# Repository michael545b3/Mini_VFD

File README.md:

# Mini VFD based on STM32

This project is a compact Variable Frequency Drive (VFD) built around an  
STM32 microcontroller and an ST IPM (Intelligent Power Module).  
It is designed to control small AC motors efficiently and safely in a compact form factor.

---

## Hardware Overview

### Core Components
- **STM32F407** microcontroller
- **STGIPN3H60** IPM (Intelligent Power Module)
- **High-voltage measurement**
- **Analog inputs** for control signals
- **Opto-isolated digital inputs**
- **Relay output**
- **EEPROM** for parameter storage

### Power Supply
- **Flyback converter** for isolated supply
- **E-Fuse** for protection
- **Buck converter** with **LDOs** for logic power

### User Interface
- **LCD display**
- **Push buttons** and **rotary encoder** for input

---

## Software Status

The firmware is currently under development. As a hardware-focused developer,  
progress is steady but slow — writing robust embedded software takes time.

So far, the implemented functions run reliably, and more features are being added continuously.  
A demonstration video will be available soon.

---

## Roadmap / To-Do

- [ ] Motor control tuning
- [ ] UI menu system improvements
- [ ] Fault monitoring and protection
- [ ] IO implementation

---

## Contributions

Contributions, feedback, or suggestions are very welcome!

---

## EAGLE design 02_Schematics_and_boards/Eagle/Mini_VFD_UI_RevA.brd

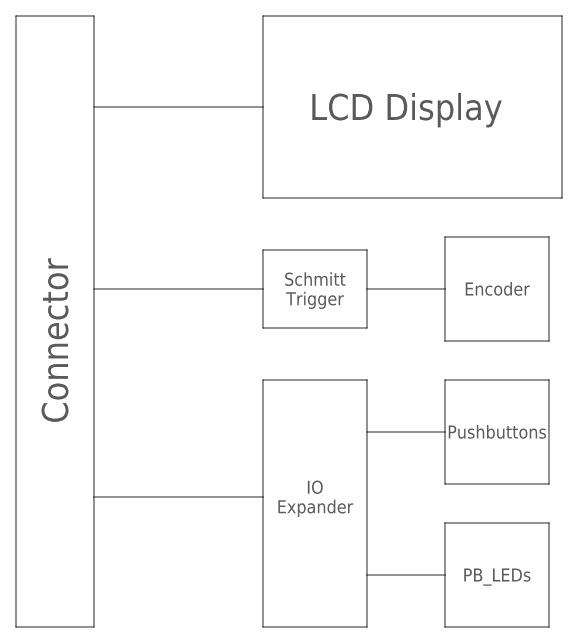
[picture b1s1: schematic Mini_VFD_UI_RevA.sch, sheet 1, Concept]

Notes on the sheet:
LCD Display
Connector
Encoder
IO Expander
Pushbuttons
PB_LEDs
Schmitt Trigger

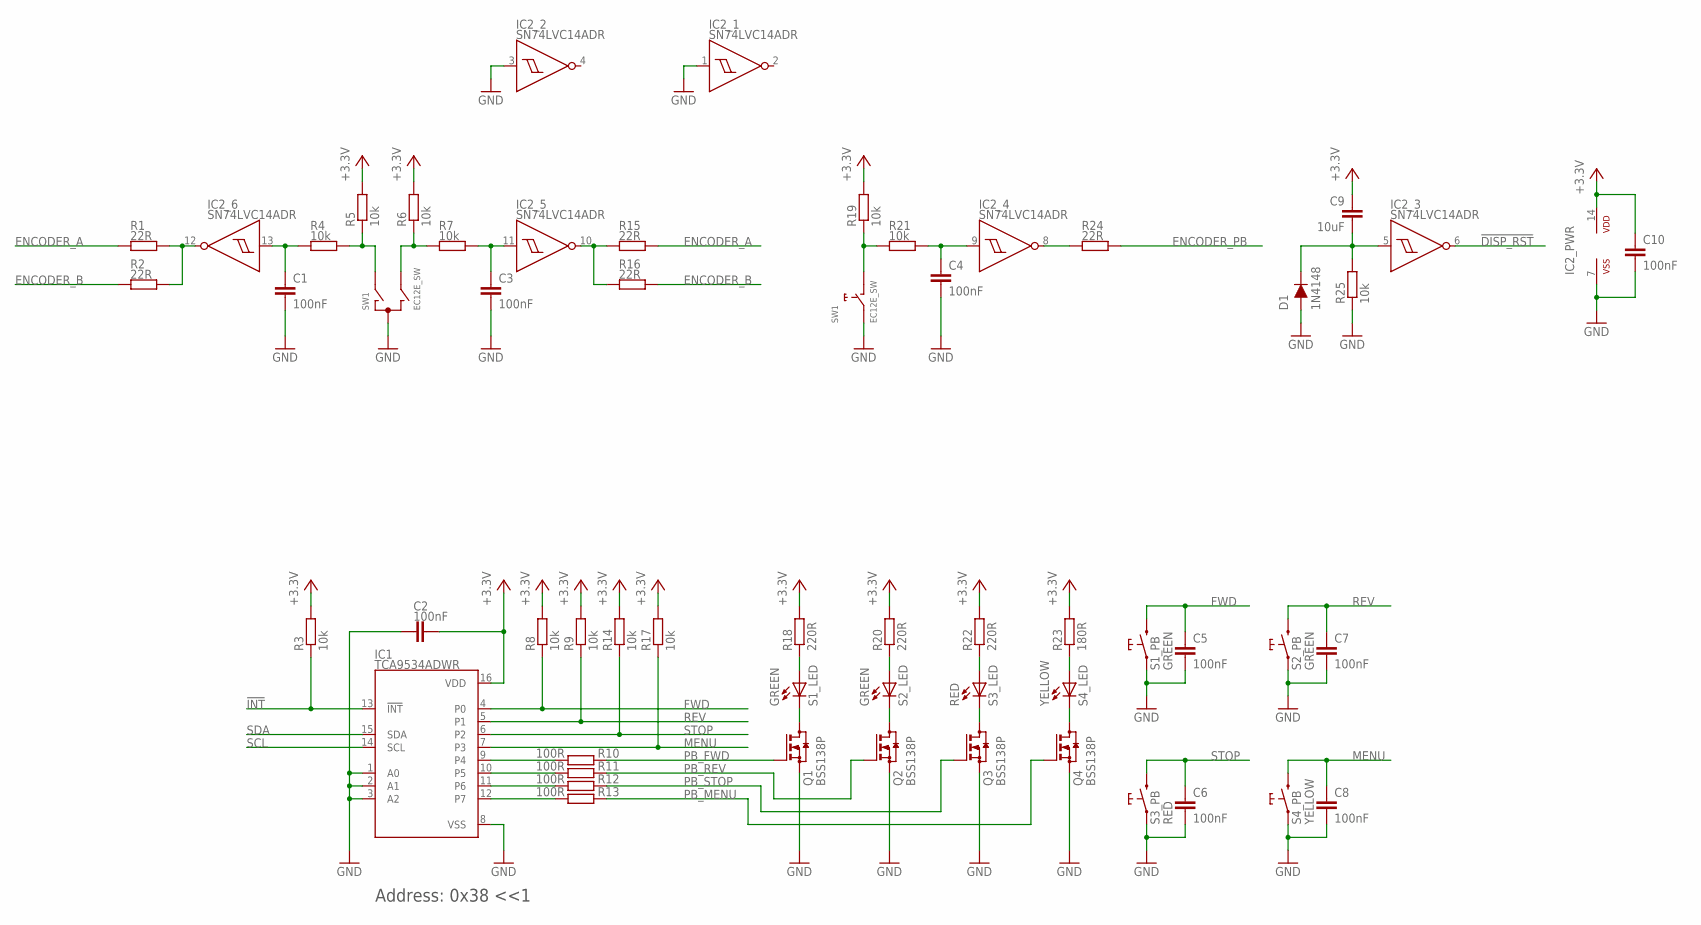
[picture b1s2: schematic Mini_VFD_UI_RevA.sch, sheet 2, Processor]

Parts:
C1, C2, C3, C4, C5, C6, C7, C8, C10: 100nF; C0603
C9: 10uF; C1206
D1: 1N4148; SOD123
IC1: TCA9534ADWR; SOIC16R
IC2: SN74LVC14ADR; SO14
Q1, Q2, Q3, Q4: BSS138P; SOT23
R1, R2, R15, R16, R24: 22R; R0603
R3, R4, R5, R6, R7, R8, R9, R14, R17, R19, R21, R25: 10k; R0603
R10, R11, R12, R13: 100R; R0603
R18, R20, R22: 220R; R0603
R23: 180R; R0603
S1, S2: GREEN; PB_ALIEXPRESS
S3: RED; PB_ALIEXPRESS
S4: YELLOW; PB_ALIEXPRESS
SW1: EC12E_SW; ALPS_EC12E_SW

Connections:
!DISP_RST: IC2.6 (O); also elsewhere on the board
!INT: IC1.13 (!INT), R3.1; also elsewhere on the board
+3.3V: C2.2, C9.1, C10.1, IC1.16 (VDD), IC2.14 (VDD), R3.2, R5.2, R6.2, R8.2, R9.2, R14.2, R17.2, R18.2, R19.2, R20.2, R22.2, R23.2; also elsewhere on the board
ENCODER_A: R1.1, R15.2; also elsewhere on the board
ENCODER_B: R2.1, R16.2; also elsewhere on the board
ENCODER_PB: R24.2; also elsewhere on the board
FWD: C5.1, IC1.4 (P0), R8.1, S1.2A (2), S1.2B (2)
GND: C1.2, C2.1, C3.2, C4.2, C5.2, C6.2, C7.2, C8.2, C10.2, D1.2 (A), IC1.1 (A0), IC1.2 (A1), IC1.3 (A2), IC1.8 (VSS), IC2.1 (I), IC2.3 (I), IC2.7 (VSS), Q1.2 (S), Q2.2 (S), Q3.2 (S), Q4.2 (S), R25.1, S1.1A (1), S1.1B (1), S2.1A (1), S2.1B (1), S3.1A (1), S3.1B (1), S4.1A (1), S4.1B (1), SW1.C, SW1.E (2); also elsewhere on the board
MENU: C8.1, IC1.7 (P3), R17.1, S4.2A (2), S4.2B (2)
unnamed: R4.2, R5.1, SW1.A
unnamed: R6.1, R7.1, SW1.B
unnamed: C1.1, IC2.13 (I), R4.1
unnamed: C3.1, IC2.11 (I), R7.2
unnamed: R19.1, R21.1, SW1.D (1)
unnamed: C4.1, IC2.9 (I), R21.2
unnamed: IC2.10 (O), R15.1, R16.1
unnamed: IC2.12 (O), R1.2, R2.2
unnamed: C9.2, D1.1 (C), IC2.5 (I), R25.2
unnamed: IC1.12 (P7), R13.1
unnamed: IC1.11 (P6), R12.1
unnamed: IC1.10 (P5), R11.1
unnamed: IC1.9 (P4), R10.1
unnamed: Q1.3 (D), S1.- (C)
unnamed: Q2.3 (D), S2.- (C)
unnamed: Q3.3 (D), S3.- (C)
unnamed: Q4.3 (D), S4.- (C)
unnamed: R18.1, S1.+ (A)
unnamed: R20.1, S2.+ (A)
unnamed: R22.1, S3.+ (A)
unnamed: R23.1, S4.+ (A)
unnamed: IC2.8 (O), R24.1
PB_FWD: Q1.1 (G), R10.2
PB_MENU: Q4.1 (G), R13.2
PB_REV: Q2.1 (G), R11.2
PB_STOP: Q3.1 (G), R12.2
REV: C7.1, IC1.5 (P1), R9.1, S2.2A (2), S2.2B (2)
SCL: IC1.14 (SCL); also elsewhere on the board
SDA: IC1.15 (SDA); also elsewhere on the board
STOP: C6.1, IC1.6 (P2), R14.1, S3.2A (2), S3.2B (2)

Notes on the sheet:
Address: 0x38 <<1

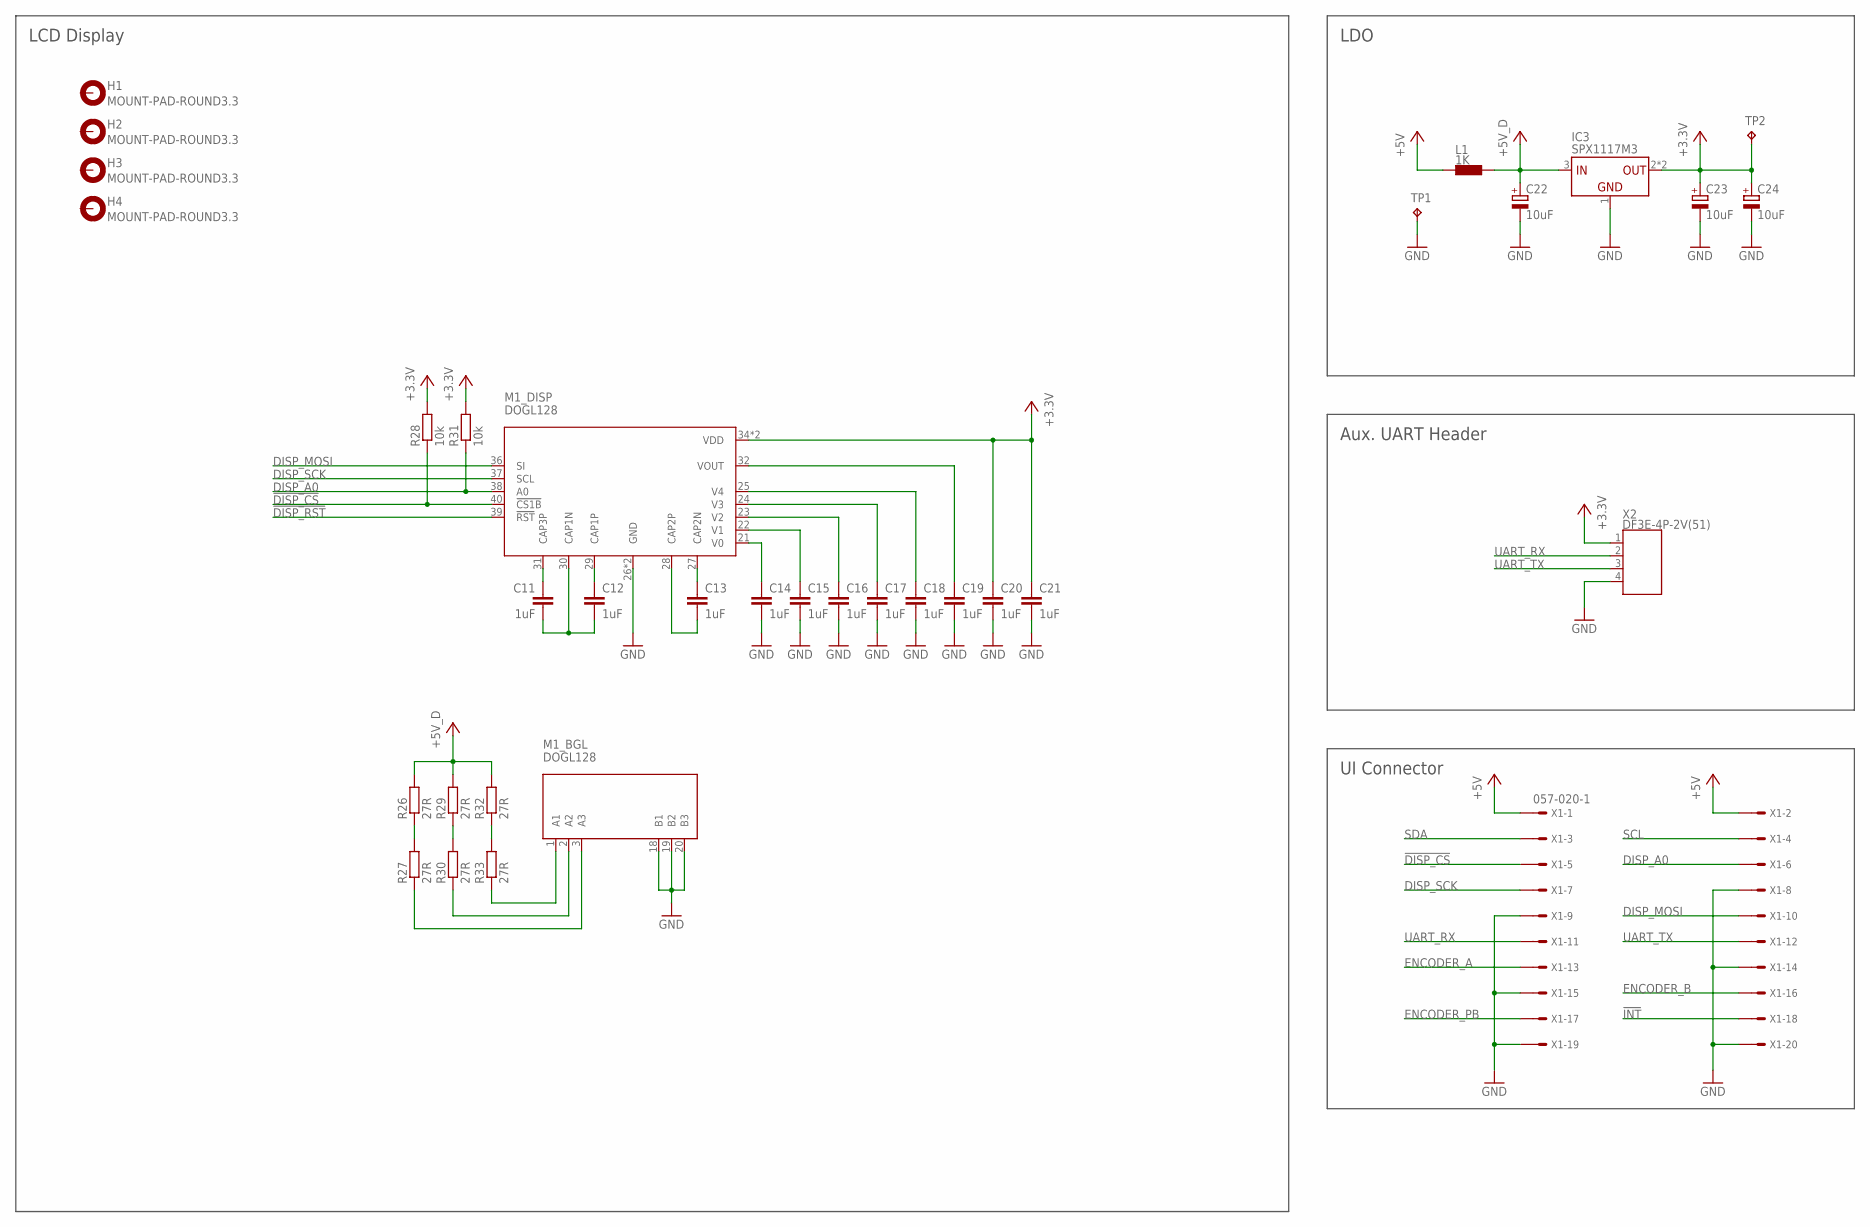
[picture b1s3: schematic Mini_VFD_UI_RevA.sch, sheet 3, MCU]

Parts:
C11, C12, C13, C14, C15, C16, C17, C18, C19, C20, C21: 1uF; C0603
C22, C23, C24: 10uF; CT3528
H1, H2, H3, H4: MOUNT-PAD-ROUND3.3; 3,3-PAD
IC3: SPX1117M3; SOT223
L1: 1K; R0603
M1: DOGL128; DOGL128-6
R26, R27, R29, R30, R32, R33: 27R; R1206
R28, R31: 10k; R0603
TP1, TP2: TPTP10R; TP10R
X1: 057-020-1
X2: DF3E-4P-2V(51); DF3E-4P-2V

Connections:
!DISP_CS: M1.40 (!CS1B), R28.1, X1.5
!DISP_RST: M1.39 (!RST); also elsewhere on the board
!INT: X1.18; also elsewhere on the board
+3.3V: C20.1, C21.1, C23.+, C24.+, IC3.2 (VOUT), IC3.4 (VOUT), M1.34 (VDD), M1.35 (VDD), R28.2, R31.2, TP2.TP, X2.1; also elsewhere on the board
+5V: L1.2, X1.1, X1.2
+5V_D: C22.+, IC3.3 (VIN), L1.1, R26.2, R29.2, R32.2
DISP_A0: M1.38 (A0), R31.1, X1.6
DISP_MOSI: M1.36 (SI), X1.10
DISP_SCK: M1.37 (SCL), X1.7
ENCODER_A: X1.13; also elsewhere on the board
ENCODER_B: X1.16; also elsewhere on the board
ENCODER_PB: X1.17; also elsewhere on the board
GND: C14.2, C15.2, C16.2, C17.2, C18.2, C19.2, C20.2, C21.2, C22.-, C23.-, C24.-, IC3.1 (GND), M1.18 (B1), M1.19 (B2), M1.20 (B3), M1.26 (GND), M1.33 (GND), TP1.TP, X1.8, X1.9, X1.14, X1.15, X1.19, X1.20, X2.4; also elsewhere on the board
unnamed: C13.2, M1.28 (CAP2P)
unnamed: C13.1, M1.27 (CAP2N)
unnamed: C12.1, M1.29 (CAP1P)
unnamed: C11.2, C12.2, M1.30 (CAP1N)
unnamed: C11.1, M1.31 (CAP3P)
unnamed: C14.1, M1.21 (V0)
unnamed: C15.1, M1.22 (V1)
unnamed: C16.1, M1.23 (V2)
unnamed: C17.1, M1.24 (V3)
unnamed: C18.1, M1.25 (V4)
unnamed: C19.1, M1.32 (VOUT)
unnamed: R26.1, R27.2
unnamed: M1.3 (A3), R27.1
unnamed: M1.2 (A2), R30.1
unnamed: M1.1 (A1), R33.1
unnamed: R29.1, R30.2
unnamed: R32.1, R33.2
SCL: X1.4; also elsewhere on the board
SDA: X1.3; also elsewhere on the board
UART_RX: X1.11, X2.2
UART_TX: X1.12, X2.3

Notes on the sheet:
LDO
LCD Display
UI Connector
Aux. UART Header

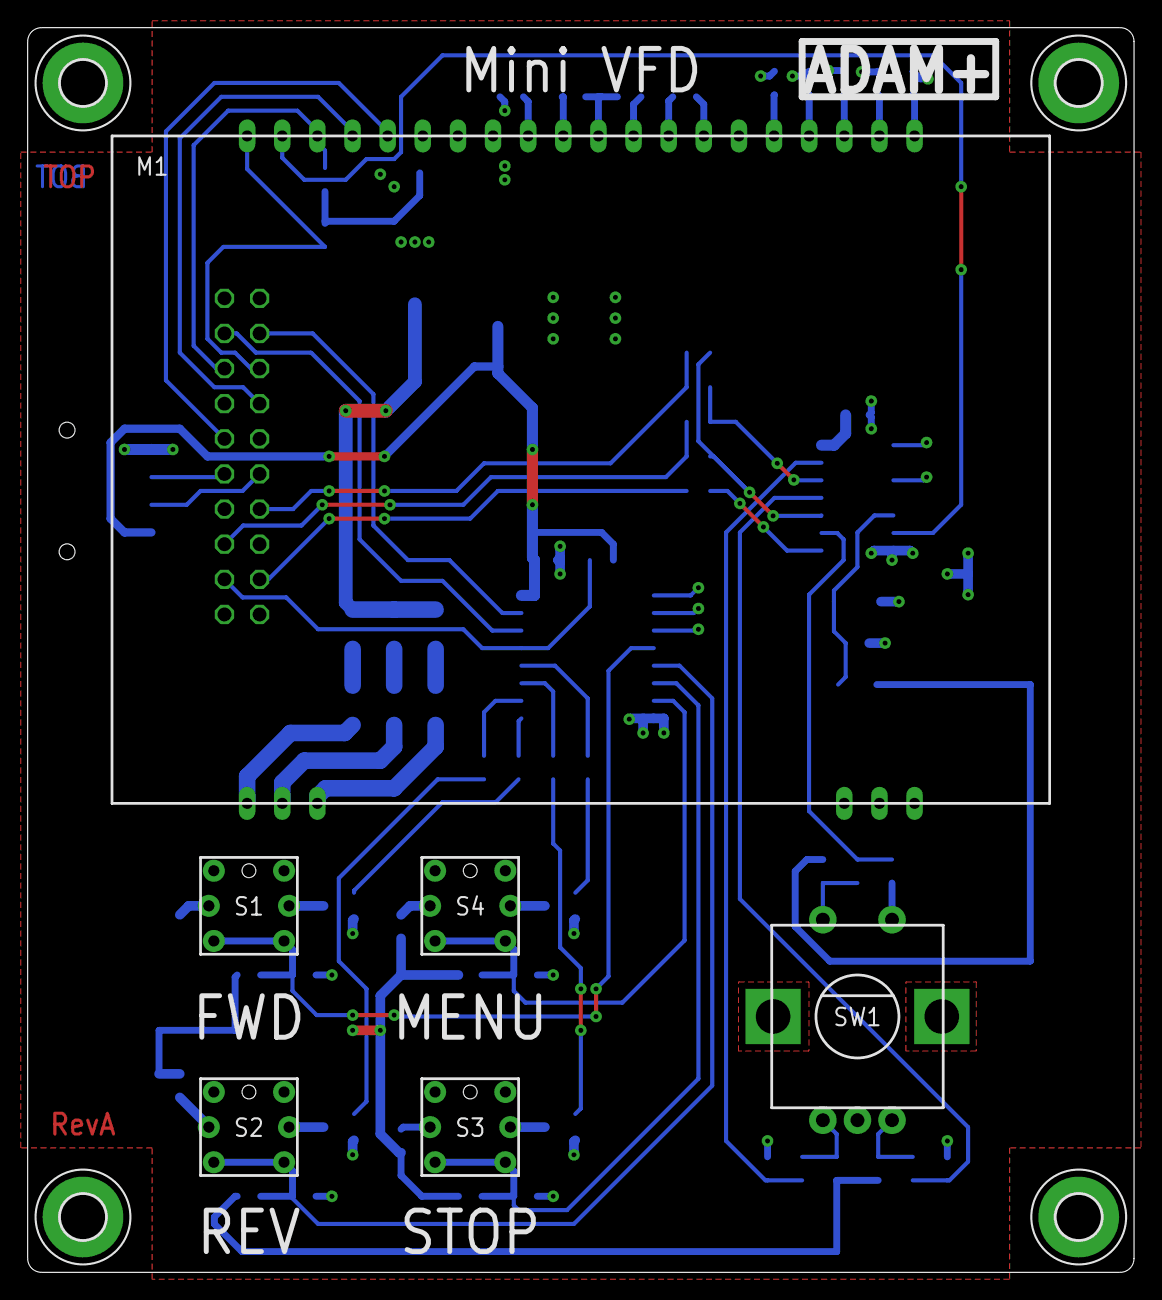
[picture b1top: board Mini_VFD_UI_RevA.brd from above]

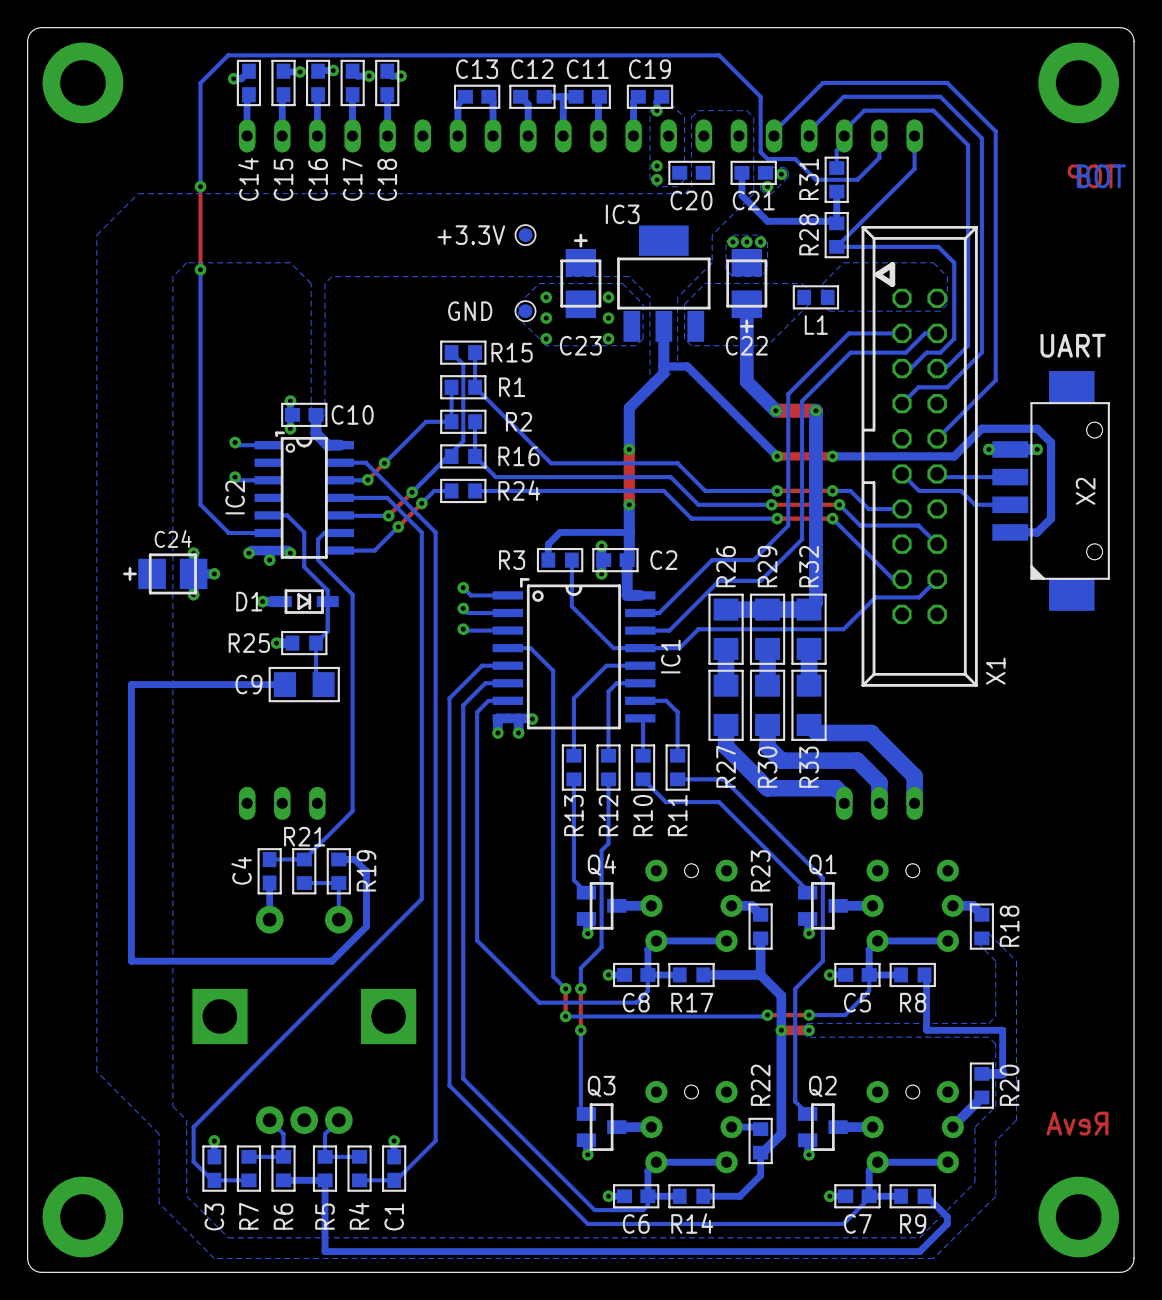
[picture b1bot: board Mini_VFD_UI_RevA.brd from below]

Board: 2 copper layers, 80.0 x 90.0 mm, 80 parts (70 on the bottom side), 64 nets.

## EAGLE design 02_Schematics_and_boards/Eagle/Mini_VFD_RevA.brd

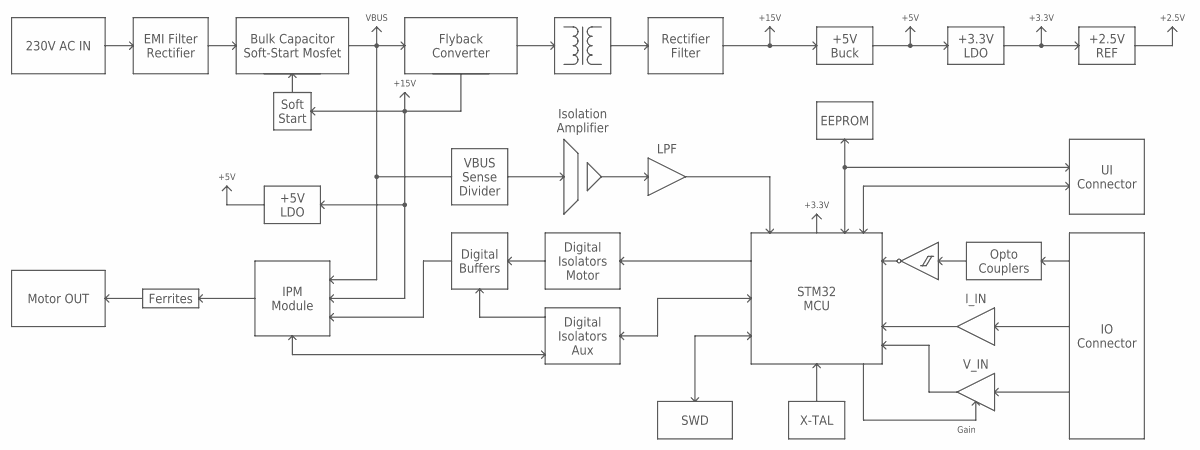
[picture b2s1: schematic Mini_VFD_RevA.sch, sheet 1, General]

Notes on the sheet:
230V AC IN
EMI Filter Rectifier
Bulk Capacitor Soft-Start Mosfet
Soft Start
Flyback Converter
Rectifier Filter
VBUS
+15V
IPM Module
+5V Buck
+3.3V LDO
+5V
+3.3V
Motor OUT
Ferrites
Digital Isolators Motor
STM32 MCU
Opto Couplers
IO Connector
X-TAL
SWD
Digital Buffers
Digital Isolators Aux
+2.5V REF
+2.5V
VBUS Sense Divider
Isolation Amplifier
LPF
I_IN
V_IN
Gain
EEPROM
UI Connector
+5V LDO

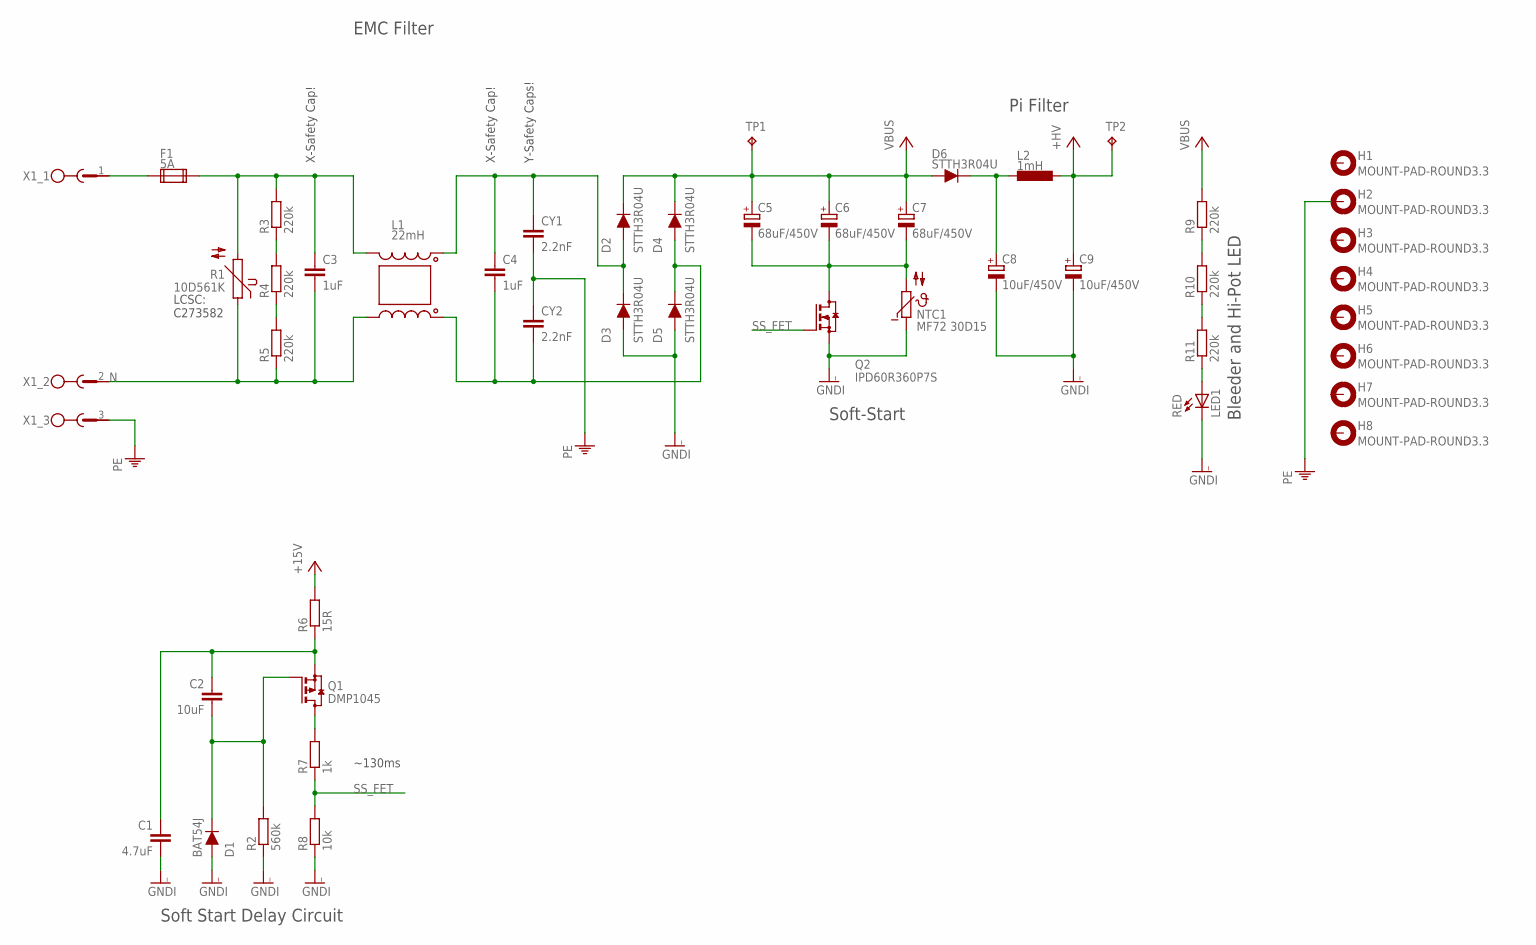
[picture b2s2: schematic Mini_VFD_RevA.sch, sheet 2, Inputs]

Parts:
C1: 4.7uF; C0805
C2: 10uF; C0805
C3, C4: 1uF; C102-082X133
C5, C6, C7: 68uF/450V; E7,5-18
C8, C9: 10uF/450V; E5-10,5
CY1, CY2: 2.2nF; YC7B5
D1: BAT54J; SOD123
D2, D3, D4, D5, D6: STTH3R04U; SMB
F1: 5A; SH25
H1, H2, H3, H4, H5, H6, H7, H8: MOUNT-PAD-ROUND3.3; 3,3-PAD
L1: 22mH; CMC_PDMCAT18107
L2: 1mH; SLH0704
LED1: RED; LED_0805
NTC1: MF72 30D15; MF72
Q1: DMP1045; SOT23
Q2: IPD60R360P7S; TO252
R1: 10D561K; S10K175
R2: 560k; R0603
R3, R4, R5, R9, R10, R11: 220k; R1206
R6: 15R; 0207/10
R7: 1k; R0603
R8: 10k; R0603
TP1, TP2: TPTP10R; TP10R
X1: MSTBV3

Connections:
+15V: R6.2; also elsewhere on the board
+HV: C9.+, L2.1, TP2.TP; also elsewhere on the board
C_NEG: C5.-, C6.-, C7.-, NTC1.2, Q2.3 (D)
GNDI: C1.2, C8.-, C9.-, D1.2 (A), D3.A, D5.A, LED1.C, NTC1.1, Q2.2 (S), R2.1, R8.1; also elsewhere on the board
L: F1.1, X1.1
L_FILT: C4.1, CY1.1, D2.A, D3.C, L1.IN1
L_FUSED: C3.1, F1.2, L1.OUT1, R1.2, R3.2
N: C3.2, L1.OUT2, R1.1, R5.1, X1.2
unnamed: Q1.3 (D), R7.2
unnamed: C2.2, D1.1 (C), Q1.1 (G), R2.2
unnamed: C1.1, C2.1, Q1.2 (S), R6.1
unnamed: R3.1, R4.2
unnamed: R4.1, R5.2
unnamed: R9.1, R10.2
unnamed: R10.1, R11.2
unnamed: LED1.A, R11.1
N_FILT: C4.2, CY2.2, D4.A, D5.C, L1.IN2
PE: CY1.2, CY2.1, H2.B3,3, X1.3; also elsewhere on the board
SS_FET: Q2.1 (G), R7.1, R8.2
VBUS: C5.+, C6.+, C7.+, D2.C, D4.C, D6.A, R9.2, TP1.TP; also elsewhere on the board
VBUS_FILT: C8.+, D6.C, L2.2

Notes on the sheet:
LCSC: C273582
X-Safety Cap!
Y-Safety Caps!
Soft-Start
Pi Filter
Bleeder and Hi-Pot LED
Soft Start Delay Circuit
~130ms
EMC Filter

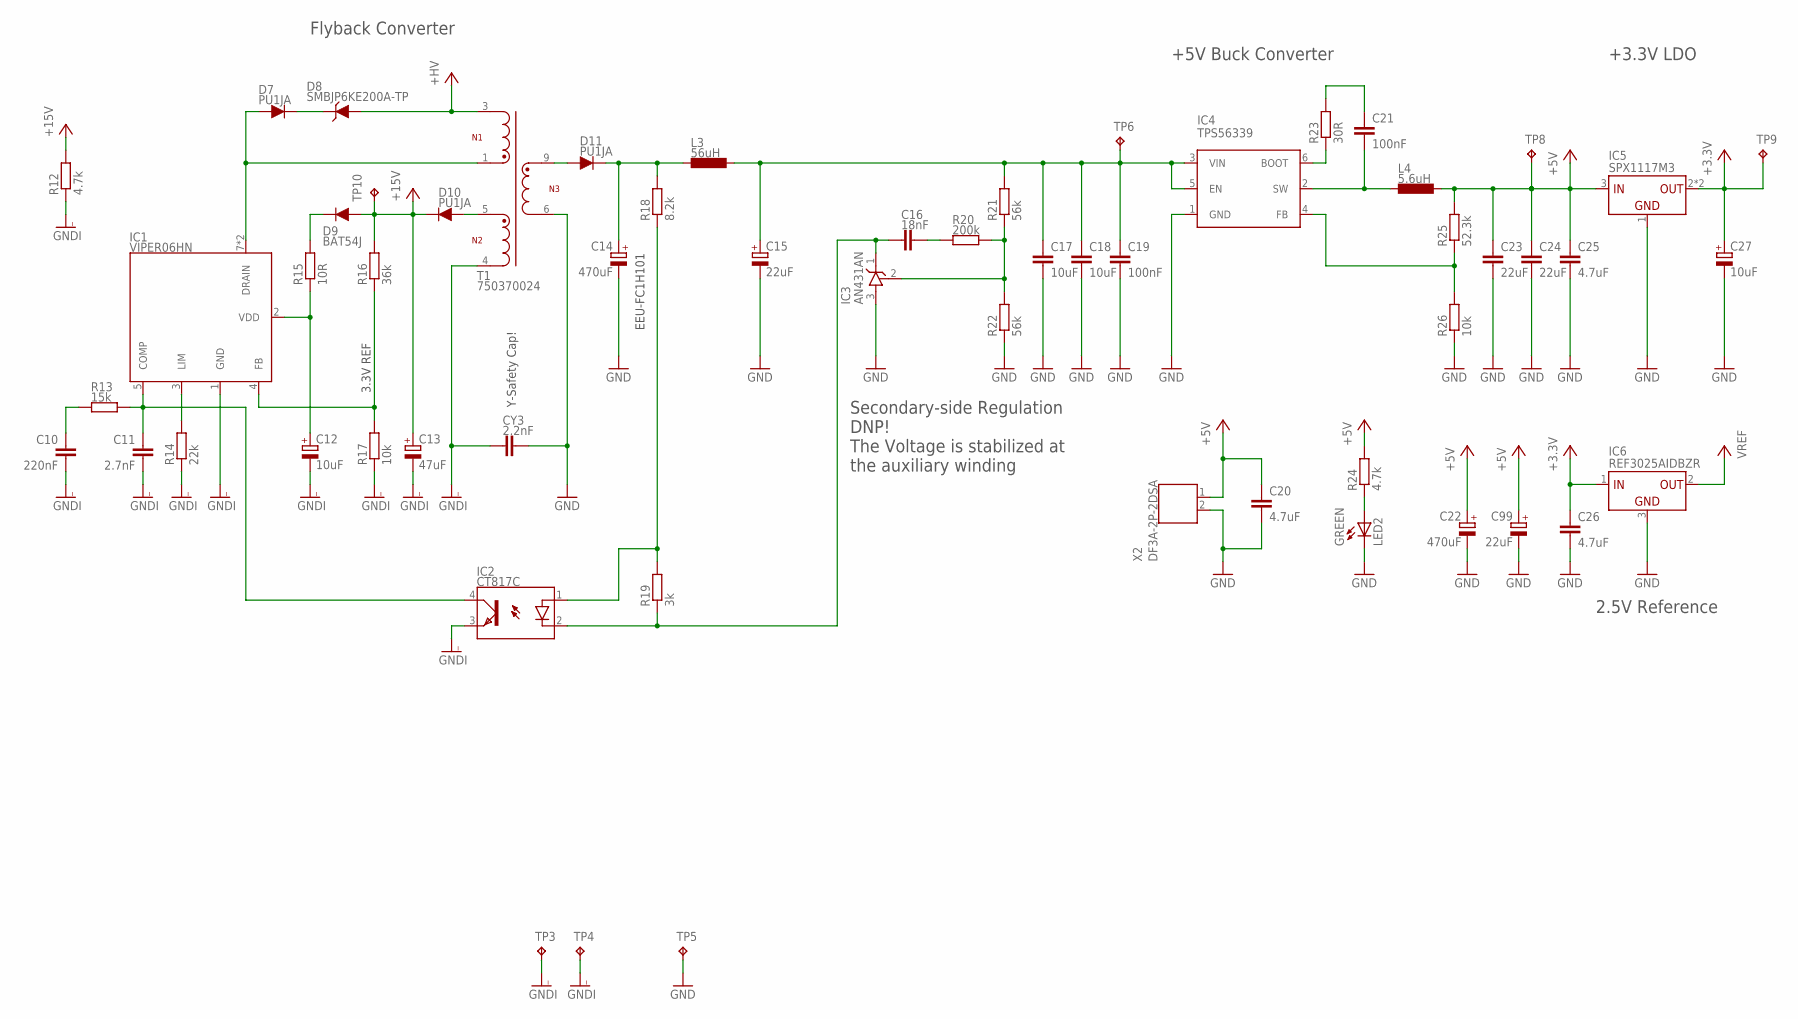
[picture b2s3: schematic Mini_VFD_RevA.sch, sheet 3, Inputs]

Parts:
C10: 220nF; C0603
C11: 2.7nF; C0603
C12: 10uF; E2,5-5
C13: 47uF; E2,5-7
C14, C22: 470uF; E5-10,5
C15, C99: 22uF; E2-5
C16: 18nF; C0603
C17, C18: 10uF; C1206
C19, C21: 100nF; C0603
C20: 4.7uF; C0805
C23, C24: 22uF; C1206
C25, C26: 4.7uF; C0603
C27: 10uF; CT3528
CY3: 2.2nF; YC7B5
D7, D10, D11: PU1JA; DO214AC
D8: SMBJP6KE200A-TP; SMB
D9: BAT54J; SOD123
IC1: VIPER06HN; DIL07
IC2: CT817C; SMD4
IC3: AN431AN; SOT23
IC4: TPS56339; TSOT23-6
IC5: SPX1117M3; SOT223
IC6: REF3025AIDBZR; SOT23
L3: 56uH; PDPTAT
L4: 5.6uH; DH0530H
LED2: GREEN; LED_0805
R12: 4.7k; R1206
R13: 15k; R0603
R14: 22k; R0603
R15: 10R; R0805
R16: 36k; R0603
R17, R26: 10k; R0603
R18: 8.2k; R0603
R19: 3k; R0603
R20: 200k; R0603
R21, R22: 56k; R0603
R23: 30R; R0603
R24: 4.7k; R0603
R25: 52.3k; R0603
T1: 750370024; WE-OLSTM_EE13_L13.72W20.45H10.8
TP3, TP4, TP5, TP6, TP8, TP9, TP10: TP_SOLDREYE; SOLDER_EYE
X2: DF3A-2P-2DSA

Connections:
+3.3V: C26.1, C27.+, IC5.2 (VOUT), IC5.4 (VOUT), IC6.1 (VIN), TP9.1; also elsewhere on the board
+5V: C20.1, C22.+, C23.1, C24.1, C25.1, C99.+, IC5.3 (VIN), L4.P$1 (1), R24.2, R25.2, TP8.1, X2.1; also elsewhere on the board
+15V: C13.+, D9.2 (A), D10.C, R12.2, R16.2, TP10.1; also elsewhere on the board
+HV: D8.A, T1.3; also elsewhere on the board
AUX_OUT: D10.A, T1.5
BOOT_+5V: IC4.6 (BOOT), R23.1
D: D7.A, IC1.7 (DRAIN), IC1.8 (DRAIN), T1.1
FB: IC4.4 (FB), R25.1, R26.2
GND: C14.-, C15.-, C17.2, C18.2, C19.2, C20.2, C22.-, C23.2, C24.2, C25.2, C26.2, C27.-, C99.-, CY3.2, IC3.3 (A), IC4.1 (GND), IC5.1 (GND), IC6.3 (GND), LED2.C, R22.1, R26.1, T1.6, TP5.1, X2.2; also elsewhere on the board
GNDI: C10.2, C11.2, C12.-, C13.-, CY3.1, IC1.1 (GND), IC2.3 (EMIT), R12.1, R14.1, R17.1, T1.4, TP3.1, TP4.1; also elsewhere on the board
unnamed: D9.1 (C), R15.2
unnamed: IC1.3 (LIM), R14.2
unnamed: IC1.4 (FB), R16.1, R17.2
unnamed: C10.1, R13.1
unnamed: IC3.2 (R), R20.2, R21.1, R22.2
unnamed: D7.C, D8.C
unnamed: C11.1, IC1.5 (COMP), IC2.4 (COL), R13.2
unnamed: C16.1, IC2.2 (C), IC3.1 (C), R19.1
unnamed: IC2.1 (A), R18.1, R19.2
unnamed: LED2.A, R24.1
unnamed: C16.2, R20.1
unnamed: C21.1, R23.2
SEC_OUT: D11.A, T1.9
SW: C21.2, IC4.2 (SW), L4.P$2 (2)
VDD: C14.+, D11.C, L3.2, R18.2
VDD_FILT: C15.+, C17.1, C18.1, C19.1, IC4.3 (VIN), IC4.5 (EN), L3.1, R21.2, TP6.1
VREF: IC6.2 (VOUT); also elsewhere on the board
V_AUX: C12.+, IC1.2 (VDD), R15.1

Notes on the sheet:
3.3V REF
EEU-FC1H101
+5V Buck Converter
+3.3V LDO
Flyback Converter
Secondary-side Regulation DNP! The Voltage is stabilized at the auxiliary winding
2.5V Reference
Y-Safety Cap!

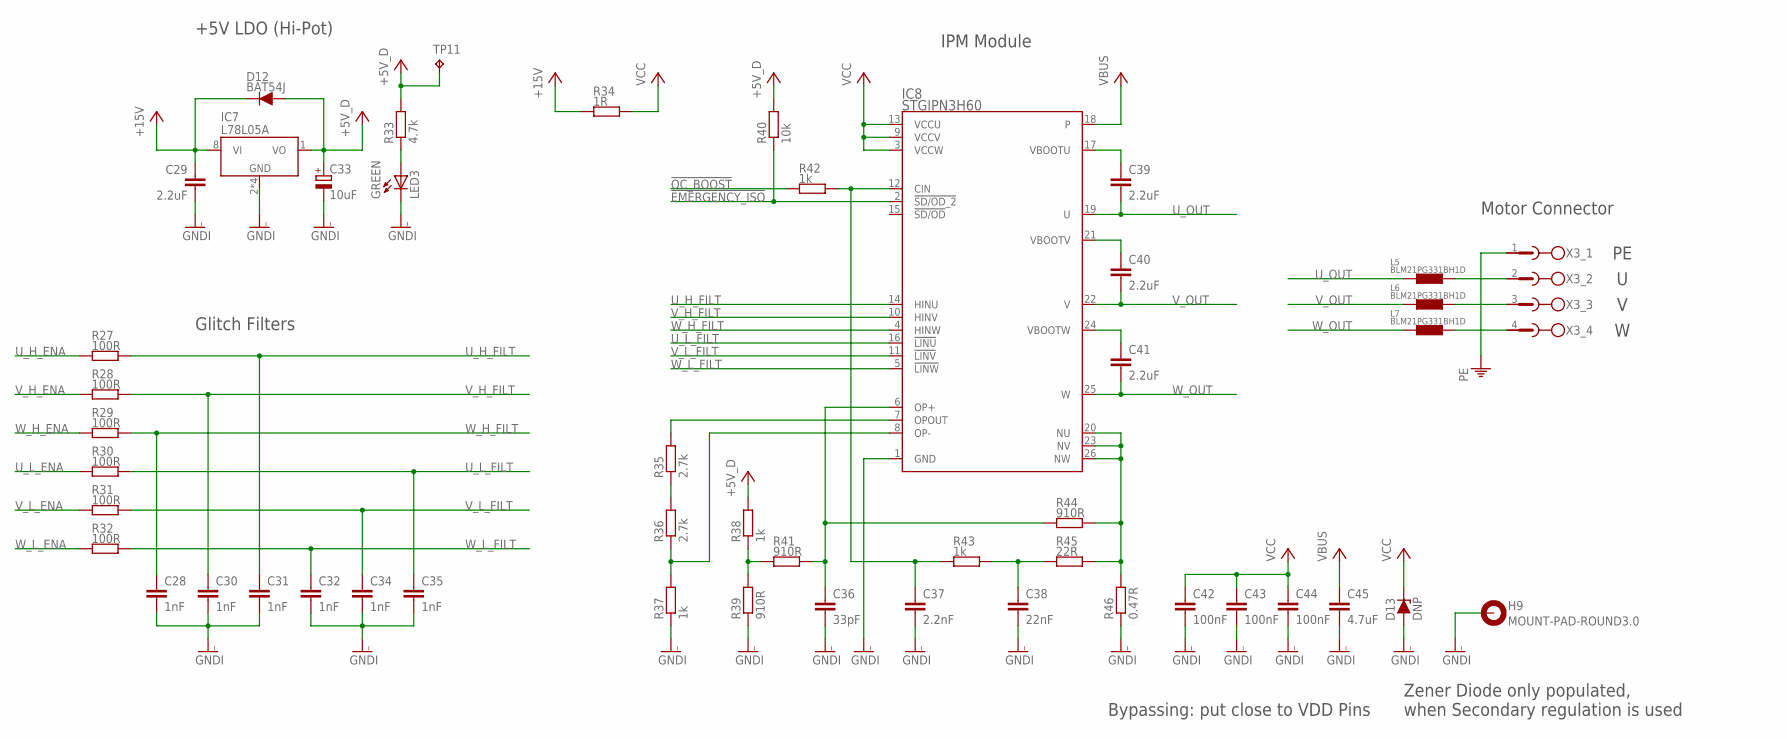
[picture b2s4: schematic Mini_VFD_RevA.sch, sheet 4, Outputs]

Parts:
C28, C30, C31, C32, C34, C35: 1nF; C0603
C29, C39, C40, C41: 2.2uF; C0805
C33: 10uF; CT3528
C36: 33pF; C0603
C37: 2.2nF; C0603
C38: 22nF; C0603
C42, C43, C44: 100nF; C0603
C45: 4.7uF; C275-126X316
D12: BAT54J; SOD123
D13: DNP; DO214AC
H9: MOUNT-PAD-ROUND3.0; 3,0-PAD
IC7: L78L05A; SOIC8
IC8: STGIPN3H60; NDIP26_12P45X29P25_STM
L5, L6, L7: BLM21PG331BH1D; R0805
LED3: GREEN; LED_0805
R27, R28, R29, R30, R31, R32: 100R; R0603
R33: 4.7k; R0603
R34: 1R; R0805
R35, R36: 2.7k; R0603
R37, R38, R42, R43: 1k; R0603
R39, R41, R44: 910R; R0603
R40: 10k; R0603
R45: 22R; R0603
R46: 0.47R; R2512
TP11: TP_SOLDREYE; SOLDER_EYE
X3: MSTBV4MTSV; MSTBV4

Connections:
!EMERGENCY_ISO: IC8.2 (!SD/OD_2), R40.1; also elsewhere on the board
!OC_BOOST: R42.1; also elsewhere on the board
+5V_D: C33.+, D12.2 (A), IC7.1 (VO), R33.2, R38.2, R40.2, TP11.1; also elsewhere on the board
+15V: C29.1, D12.1 (C), IC7.8 (VI), R34.1; also elsewhere on the board
BOOT_U: C39.1, IC8.17 (VBOOTU)
BOOT_V: C40.1, IC8.21 (VBOOTV)
BOOT_W: C41.1, IC8.24 (VBOOTW)
GNDI: C28.2, C29.2, C30.2, C31.2, C32.2, C33.-, C34.2, C35.2, C36.2, C37.2, C38.2, C42.2, C43.2, C44.2, C45.2, D13.A, H9.B3,0, IC7.2 (GND), IC7.3 (GND), IC7.6 (GND), IC7.7 (GND), IC8.1 (GND), LED3.C, R37.1, R39.1, R46.1; also elsewhere on the board
unnamed: LED3.A, R33.1
unnamed: C38.1, R43.2, R45.1
unnamed: C37.1, IC8.12 (CIN), R42.2, R43.1
unnamed: IC8.8 (OP-), R36.1, R37.2
unnamed: R35.1, R36.2
unnamed: IC8.7 (OPOUT), R35.2
unnamed: R38.1, R39.2, R41.1
unnamed: C36.1, IC8.6 (OP+), R41.2, R44.1
N_COM: IC8.20 (NU), IC8.23 (NV), IC8.26 (NW), R44.2, R45.2, R46.2
PE: X3.1; also elsewhere on the board
U: L5.2, X3.2
U_H_ENA: R27.1; also elsewhere on the board
U_H_FILT: C31.1, IC8.14 (HINU), R27.2
U_L_ENA: R30.1; also elsewhere on the board
U_L_FILT: C35.1, IC8.16 (!LINU), R30.2
U_OUT: C39.2, IC8.19 (U), L5.1
V: L6.2, X3.3
VBUS: C45.1, IC8.18; also elsewhere on the board
VCC: C42.1, C43.1, C44.1, D13.C, IC8.3 (VCCW), IC8.9 (VCCV), IC8.13 (VCCU), R34.2
V_H_ENA: R28.1; also elsewhere on the board
V_H_FILT: C30.1, IC8.10 (HINV), R28.2
V_L_ENA: R31.1; also elsewhere on the board
V_L_FILT: C34.1, IC8.11 (!LINV), R31.2
V_OUT: C40.2, IC8.22 (V), L6.1
W: L7.2, X3.4
W_H_ENA: R29.1; also elsewhere on the board
W_H_FILT: C28.1, IC8.4 (HINW), R29.2
W_L_ENA: R32.1; also elsewhere on the board
W_L_FILT: C32.1, IC8.5 (!LINW), R32.2
W_OUT: C41.2, IC8.25 (W), L7.1

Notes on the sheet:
+5V LDO (Hi-Pot)
IPM Module
Glitch Filters
Motor Connector
Zener Diode only populated, when Secondary regulation is used
Bypassing: put close to VDD Pins

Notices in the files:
parts and their libraries:
WE-OLSTM: Copyright: Würth Elektronik
